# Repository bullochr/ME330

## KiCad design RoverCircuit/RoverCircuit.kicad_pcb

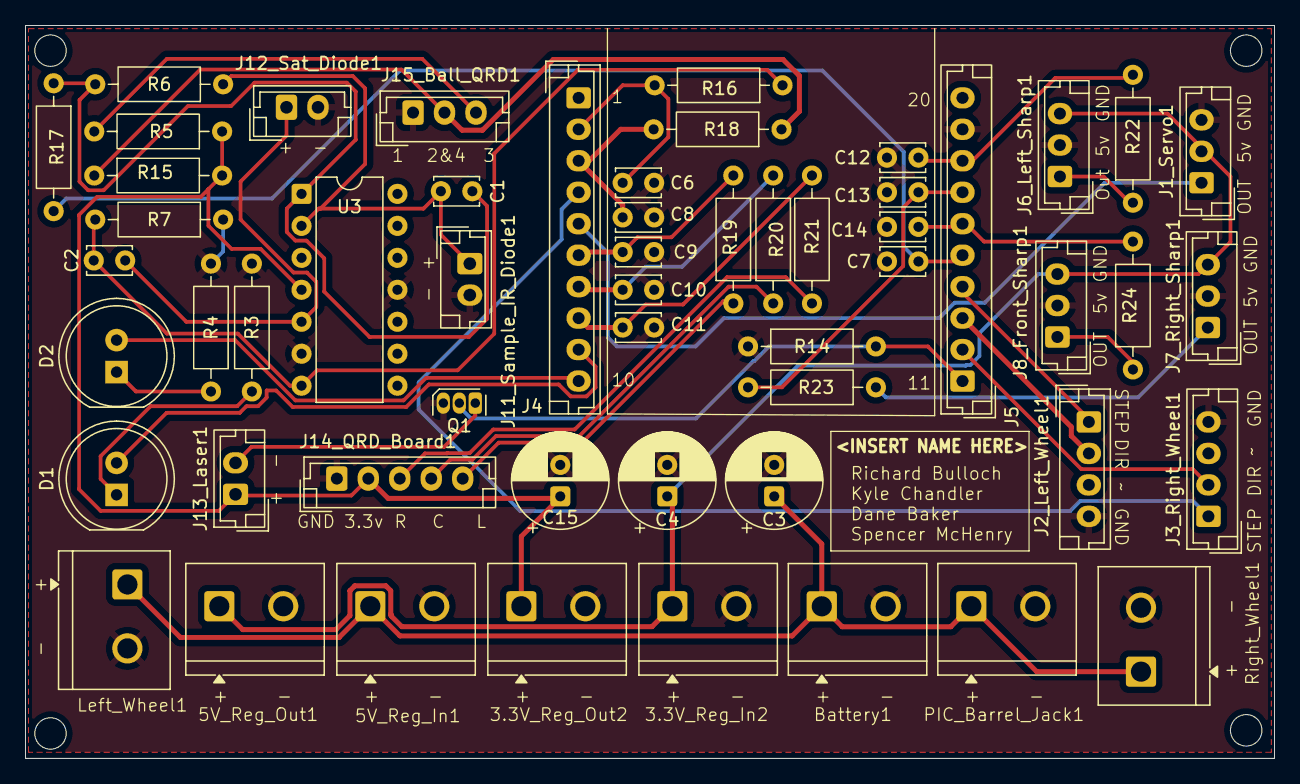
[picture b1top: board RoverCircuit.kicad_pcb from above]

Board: 2 copper layers, 99.2 x 58.2 mm, 55 parts (0 on the bottom side), 36 nets.

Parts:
3.3V_Reg_In2, 3.3V_Reg_Out2, 5V_Reg_In1, 5V_Reg_Out1: Battery_Terminal; screw_terminal
Battery1: Battery_Terminal; screw_terminal
C1, C2, C6, C7, C8, C9, C10, C11, C12, C13, C14: 0.1uF; C_Disc_D3.4mm_W2.1mm_P2.50mm
C3, C4, C15: 100uF; CP_Radial_D7.5mm_P2.50mm
D1, D2: LED; LED_D8.0mm
J1_Servo1, J6_Left_Sharp1, J7_Right_Sharp1, J8_Front_Sharp1, J15_Ball_QRD1: JST_3Pin_P2.54_V; JST_EH_B3B-EH-A_1x03_P2.50mm_Vertical
J2_Left_Wheel1, J3_Right_Wheel1: JST_4Pin_P2.54_V; JST_EH_B4B-EH-A_1x04_P2.50mm_Vertical
J4, J5: JST_10Pin_P2.54_V; JST_EH_B10B-EH-A_1x10_P2.50mm_Vertical
J11_Sample_IR_Diode1, J12_Sat_Diode1, J13_Laser1: JST_2Pin_P2.54_V; JST_EH_B2B-EH-A_1x02_P2.50mm_Vertical
J14_QRD_Board1: JST_5Pin_P2.54_V; JST_EH_B5B-EH-A_1x05_P2.50mm_Vertical
Left_Wheel1: Left_Wheel_Power_Terminal; screw_terminal
PIC_Barrel_Jack1: PIC_Power_Terminal; screw_terminal
Q1: ZVN2106A; TO-92S
R3, R4, R5: 330Ω; R_Axial_DIN0207_L6.3mm_D2.5mm_P10.16mm_Horizontal
R6, R7: 1MΩ; R_Axial_DIN0207_L6.3mm_D2.5mm_P10.16mm_Horizontal
R14, R15, R16, R17, R18, R19, R20, R21, R22, R23, R24: 10kΩ; R_Axial_DIN0207_L6.3mm_D2.5mm_P10.16mm_Horizontal
Right_Wheel1: Right_Wheel_Terminal; screw_terminal
U3: LM324; DIP-14_W7.62mm

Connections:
/3.3v_Rail: 3.3V_Reg_Out2.1, C15.1, J13_Laser1.1, J14_QRD_Board1.2, R5.1, R15.2, U3.4 (V+)
/5v_Rail: 3.3V_Reg_In2.1, 5V_Reg_Out1.1, C4.1, J1_Servo1.2, J6_Left_Sharp1.3, J7_Right_Sharp1.3, J8_Front_Sharp1.3
/12v_Rail: 5V_Reg_In1.1, Battery1.1, C3.1, Left_Wheel1.1, PIC_Barrel_Jack1.1, Right_Wheel1.1
/Ball_Color_QRD_Input: C8.1, J4.3, R18.2
/Ball_Color_QRD_Output: J15_Ball_QRD1.2, R15.1, R18.1
/Debug_LED_1: D1.2 (A), J4.9
/Debug_LED_2: D2.2 (A), J4.10
/Front_Sharp_Input: C14.1, J5.6, R24.2
/Front_Sharp_Output: J8_Front_Sharp1.1, R24.1
/Laser_Output: J5.1, Q1.2 (G), R14.2
/Left_Of_Line_QRD_Input: C9.1, J4.6, R19.2
/Left_Of_Line_QRD_Output: J14_QRD_Board1.5, R19.1
/Left_Sharp_Input: C12.1, J5.8, R22.2
/Left_Sharp_Output: J6_Left_Sharp1.1, R22.1
/Left_Wheel_DIR: J2_Left_Wheel1.2, J5.3
/Left_Wheel_Step: J2_Left_Wheel1.1, J5.4
/On_Line_QRD_Input: C10.1, J4.7, R20.2
/On_Line_QRD_Output: J14_QRD_Board1.4, R20.1
/Right_Of_Line_QRD_Input: C11.1, J4.8, R21.2
/Right_Of_Line_QRD_Output: J14_QRD_Board1.3, R21.1
/Right_Sharp_Input: C13.1, J5.7, R23.2
/Right_Sharp_Output: J7_Right_Sharp1.1, R23.1
/Right_Wheel_DIR: J3_Right_Wheel1.2, J5.2
/Right_Wheel_Step: J3_Right_Wheel1.1, J4.4
/Sample_Collection_IR_Input: C7.1, J5.5, R17.2
/Sample_Collection_IR_Output: C1.2, R6.2, R17.1, U3.1
/Satellite_IR_Input: C6.1, J4.2, R16.2
/Satellite_IR_Output: C2.2, R7.2, R16.1, U3.7
/Servo_PWM: J1_Servo1.1, J4.5
GND: 3.3V_Reg_In2.2, 3.3V_Reg_Out2.2, 5V_Reg_In1.2, 5V_Reg_Out1.2, Battery1.2, C3.2, C4.2, C6.2, C7.2, C8.2, C9.2, C10.2, C11.2, C12.2, C13.2, C14.2, C15.2, J1_Servo1.3, J2_Left_Wheel1.4, J3_Right_Wheel1.4, J5.9, J6_Left_Sharp1.2, J7_Right_Sharp1.2, J8_Front_Sharp1.2, J11_Sample_IR_Diode1.2, J12_Sat_Diode1.2, J14_QRD_Board1.1, J15_Ball_QRD1.1, Left_Wheel1.2, PIC_Barrel_Jack1.2, Q1.3 (S), R3.1, R4.1, R7.1, R14.1, Right_Wheel1.2, U3.3 (+), U3.6 (-), U3.11 (V-)
unnamed: D1.1 (K), R3.2
unnamed: D2.1 (K), R4.2
unnamed: C1.1, J11_Sample_IR_Diode1.1, R6.1, U3.2 (-)
unnamed: C2.1, J12_Sat_Diode1.1, U3.5 (+)
unnamed: J13_Laser1.2, Q1.1 (D)
unnamed: J15_Ball_QRD1.3, R5.2

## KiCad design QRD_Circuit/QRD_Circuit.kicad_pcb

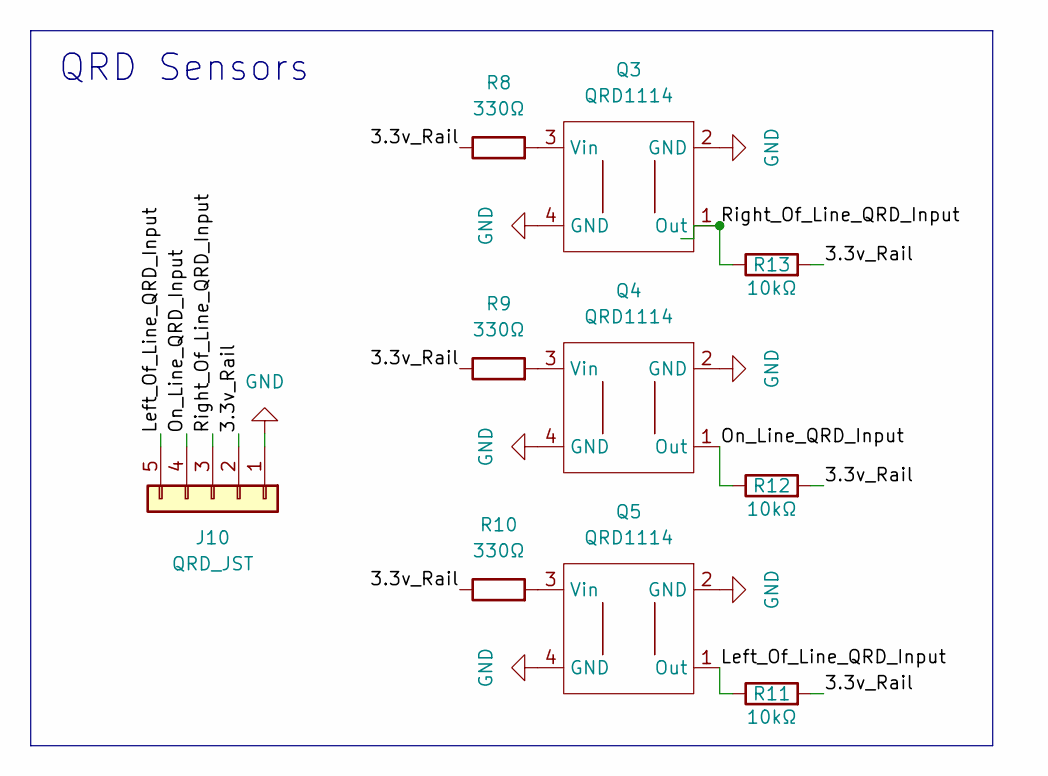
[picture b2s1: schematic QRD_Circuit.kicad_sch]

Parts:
J10: QRD_JST; JST_EH_S5B-EH_1x05_P2.50mm_Horizontal
Q3, Q4, Q5: QRD1114; Diode_Bridge_DIP-4_W5.08mm_P2.54mm
R8, R9, R10: 330Ω; R_Axial_DIN0207_L6.3mm_D2.5mm_P10.16mm_Horizontal
R11, R12, R13: 10kΩ; R_Axial_DIN0207_L6.3mm_D2.5mm_P10.16mm_Horizontal

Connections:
/3.3v_Rail: J10.2, R8.1, R9.1, R10.1, R11.2, R12.2, R13.2
/Left_Of_Line_QRD_Input: J10.5, Q5.1 (Out), R11.1
/On_Line_QRD_Input: J10.4, Q4.1 (Out), R12.1
/Right_Of_Line_QRD_Input: J10.3, Q3.1 (Out), R13.1
GND: J10.1, Q3.2 (GND), Q3.4 (GND), Q4.2 (GND), Q4.4 (GND), Q5.2 (GND), Q5.4 (GND)
unnamed: Q3.3 (Vin), R8.2
unnamed: Q4.3 (Vin), R9.2
unnamed: Q5.3 (Vin), R10.2

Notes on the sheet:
QRD Sensors

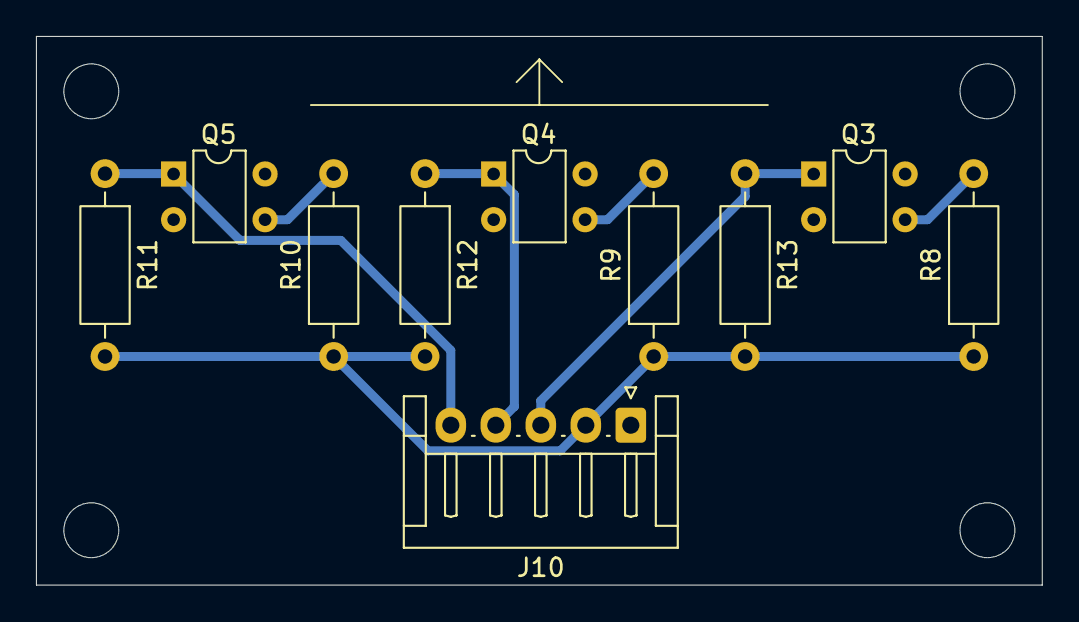
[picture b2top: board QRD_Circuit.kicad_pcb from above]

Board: 2 copper layers, 55.9 x 30.5 mm, 10 parts (0 on the bottom side), 8 nets.
